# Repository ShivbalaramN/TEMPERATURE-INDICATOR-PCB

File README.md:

**Temperature Indicator PCB**

**📌 Project Overview**

This project demonstrates a simple temperature indicator circuit designed using KiCad. The circuit uses a NTC Thermistor to detect temperature changes and a BC547 to control an LED indicator.
The LED turns ON when the temperature increases, providing a simple visual indication of temperature change.

**⚙️ Features**

 Simple temperature sensing circuit
 
 Transistor switching mechanism
 
 Custom PCB designed in KiCad
 
 Beginner-friendly electronics project
 
 Demonstrates basic sensor interfacing
 
**🧩 Components Used**

 NTC Thermistor (10kΩ)
 
 BC547
 
 LED
 
 Resistor (10kΩ)
 
 Resistor (220Ω)

2-pin power connector (5V supply)

**🔌 Working Principle**

 The NTC thermistor changes its resistance depending on temperature.
 
 When the temperature increases, the resistance of the thermistor decreases.
 
 This increases the voltage applied to the base of the BC547 transistor.
 
 The transistor turns ON, allowing current to flow from collector to emitter.
 
 Current passes through the LED and resistor, causing the LED to glow.
 
 Thus, the LED acts as a temperature indicator.
 
**🖥️ Software Used**

KiCad – Schematic design and PCB layout

**📂 Project Structure**

**Temperature-Indicator-PCB**
│
├── Schematic
├── PCB_Layout
├── Gerber_Files
└── README.md

**🎯 Applications**

 Temperature monitoring circuits

 Educational electronics projects
 
 Sensor interfacing practice
 
 Basic alarm or indicator systems

**AUTHOR**: SHIV BALARAM N ECE-DEPT ANNA UNIVERSITY

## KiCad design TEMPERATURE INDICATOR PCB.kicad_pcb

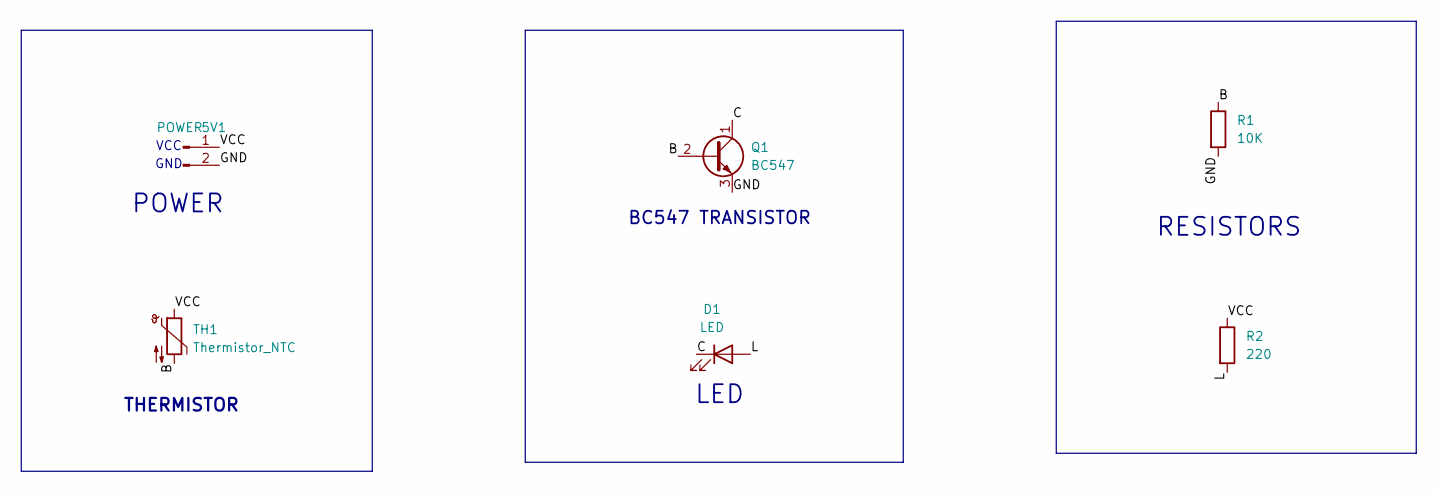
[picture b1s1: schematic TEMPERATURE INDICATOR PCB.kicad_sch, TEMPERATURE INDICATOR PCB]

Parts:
5V1: POWER; PhoenixContact_MCV_1,5_2-G-5.08_1x02_P5.08mm_Vertical
D1: LED; LED_D5.0mm
Q1: BC547; TO-92_Inline
R1: 10K; R_Axial_DIN0207_L6.3mm_D2.5mm_P7.62mm_Horizontal
R2: 220; R_Axial_DIN0207_L6.3mm_D2.5mm_P7.62mm_Horizontal
TH1: Thermistor_NTC; R_Axial_DIN0207_L6.3mm_D2.5mm_P7.62mm_Horizontal

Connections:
/B: Q1.2 (B), R1.1, TH1.2
/C: D1.1 (K), Q1.1 (C)
/GND: 5V1.2, Q1.3 (E), R1.2
/L: D1.2 (A), R2.2
/VCC: 5V1.1, R2.1, TH1.1

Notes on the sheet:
POWER
VCC
BC547 TRANSISTOR
RESISTORS
THERMISTOR
GND
LED

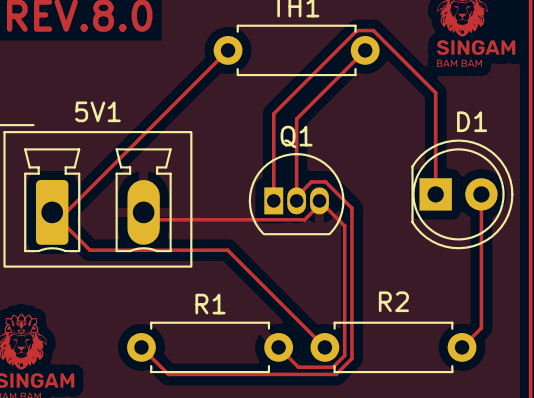
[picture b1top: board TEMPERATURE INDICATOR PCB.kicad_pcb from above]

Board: 2 copper layers, 6 parts (0 on the bottom side), 5 nets.

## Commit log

2026-03-15 Revise README for improved project overview and features
    Updated the README to enhance project details and structure.
2026-03-15 Update applications section in README
